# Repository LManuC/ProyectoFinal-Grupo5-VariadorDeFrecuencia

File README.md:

# ProyectoFinal-Grupo5-VariadorDeFrecuencia
El presente proyecto propone el desarrollo de un dispositivo electrónico capaz de alimentar un motor trifásico de hasta 1/3 HP, utilizando como fuente una tensión continua de 12V. Este conversor funciona como un variador de frecuencia, generando una salida trifásica con tensión eficaz entre fases de hasta 220 Vrms y frecuencia de salida variable entre 1 Hz y 150 Hz.
Para lograr el control del motor, se utiliza una técnica de modulación espacial (Space Vector Modulation), sin sensores montados en el eje del motor, lo que permite una instalación más sencilla, sin necesidad de encoder. El sistema está comandado por un controlador que gestiona tanto el disparo de los transistores como la interfaz de usuario y las protecciones internas.
El sistema estará contenido en una carcasa plástica especialmente diseñada para garantizar seguridad eléctrica durante la manipulación, proteger los componentes internos y permitir un montaje simple y robusto en el entorno de uso.

# Motivación
En un país como la Argentina, con grandes extensiones de tierras sin suministro eléctrico, la explotación de la energía renovable ha dado lugar a la utilización de grandes máquinas y herramientas eléctricas que tiempo atrás no hubiese sido posible. Si bien es cierto que los generadores eléctricos han dado espacio a estas instalaciones, requerían de mantenimiento periódico para que estuviesen operativas en el momento que se necesitaban, además de necesitar un material combustible que les permitiera funcionar y, en ocasiones podría generar un problema el ruido de los motores.

# Concepto del negocio
El dispositivo diseñado permitirá la conversión, acondicionamiento y regulación de la energía eléctrica para el accionamiento de un motor trifásico de baja potencia (1/3 HP) con velocidad variable generada a partir del motor de combustión interna y el alternador de equipos agrícolas o sistemas de energía solar, eólica con su correspondiente back up de energía eléctrica, posibilitando la operación de motores trifásicos destinados a tareas como sistemas de riego, transporte de materiales mediante cintas motorizadas o procesos de molienda integrados a bordo que puedan emplearse unificando todos los dispositivos que son empleados en instalaciones de energía renovable: Elevadores de tensión, inversores y variadores de frecuencia. La propuesta se enmarca en la necesidad de implementar soluciones energéticas autónomas y portátiles en entornos rurales, donde las condiciones de acceso a la red eléctrica convencional pueden ser limitadas o inexistentes.

## FODA

### Fortalezas
* La alimentación de baja tensión, nos permite meternos en un nuevo nicho. Permite trabajar con sistemas solares reducidos o baterías.
* Producto robusto y económico.
* Mantenimiento preventivo y reparación: Al conocer el diseño del equipo se puede hacer mantenimiento a los equipos y también otorgar una garantía con un taller de revisión y reparación en caso de falla.
* Productor local: Es una característica muy importante ya que el cliente tiene mayor confianza y los plazos de entrega son muchos más rápidos y económicos.
### Oportunidades
* Dada la practicidad puede ocasionar una gran demanda en zonas aisladas, remotas o rurales que se encuentren offgrid.
* Dado que es un único producto de su clase podría aparecer un nuevo rubro o sector diferente en donde encuentre utilidad. 
* El desarrollo nacional nos puede dar ventajas en licitaciones públicas o incentivos tecnológicos del gobierno.
### Debilidades
* Falta de experiencia y desconocimiento del producto puede desalentar o generar desconfianza en el producto.
* La robustez es muy importante en un controlador de un motor, se necesitan años de estudio riguroso del comportamiento y testeo del equipo para asegurar un funcionamiento ejemplar.
* La certificación eléctrica es un aspecto crucial en un equipo de esta clase y estas son muy costosas.
### Amenazas
* Posibilidad de la aparición de competencia con mejores precios y más funcionalidades.
* La escalabilidad no siempre es tan lineal, si aumenta mucho el mercado puede ocurrir que la inversión sea grande.
* El soporte post venta debe funcionar bien ya que en caso de una respuesta lenta al cliente podría perjudicar a la reputación de la marca.

# Alcance
El alcance del proyecto quedará definido en lograr, a partir de una fuente de de 12V de corriente contínua, el accionamiento de un motor trifásico de ⅓ de HP, variar su velocidad de giro, programar sesiones de trabajo diario, informar por señales típicas de 0-10V la velocidad de operación del motor, parada de emergencia, configuración de velocidades a través de un selector.

## Características eléctricas del dispositivo
Vin: 12VDC
Vout: 3 x 220VAC
fout: 0Hz - 150Hz
Pmax: 375W / 1/2HP

# Riesgos
1.  Fallas en la elección de la topología:
    -  Priorización del diseño frente a otras tareas;
    -  Ensayos varios sobre circuitos físicos;
2.  Rendimiento simulado insuficiente
    -  Priorización del diseño frente a otras tareas;
    -  Ensayos varios sobre circuitos físicos;
    -  Pruebas sobre motores utilizando variadores de frecuencia comerciales con entrada de contínua;
3.  No se consiguen los materiales en el mercado local
    -  Diseño temprano de PCB
    -  Compra en exceso de dispositivos críticos
4.  El transformador está mal construído y no entrega la potencia necesaria
    -  Fabricación de transformador con un proveedor especializado
5.  Al PCB le faltaron rutear una o más pistas
    -  Validaciones cruzadas de footprints
    -  Validaciones cruzadas de esquemáticos
    -  Validaciones cruzadas de PCB
6.  Pérdida de componentes
    -  Compra en exceso de dispositivos críticos
    -  Compra en exceso de dispositivos pequeños
    -  Compra en exceso de dispositivos sin marking
7.  Error en el diseño del footprint
    -  Validaciones cruzadas de footprints
    -  Checkbox en componentes para registrar validación
    -  Agregado de hoja de datos al esquemático
    -  Agregado de nombre del componente según el fabricante
8.  Errores de diseño hacen que la tensión no sea lo suficientemente alta
    -  Diseño autodefensivo con tensiones sobredimensionadas
    -  Cálculo de convertido con duty de respaldo
9. Rotura del banco de pruebas
    -  Fabricación de partes críticas de repuesto
    -  Colaboración externa especializada
10. Dificultades para simular el desfasaje
    -  Sobreestimación de los tiempos de trabajo
11. Error en el cálculo de la corriente máxima de algún componente y la corriente quedó sobredimensionada
    -  Justificación y documentación de los componentes elegidos
    -  Compra en exceso de dispositivos críticos
12. Falla el circuito y se quema una de las placas de potencia
    -  Fabricación de placa extra
    -  Compra en exceso de dispositivos críticos
    -  Circuitería de protección ruteada sin montar
13. El transformador está mal calculado y no entrega la potencia necesaria
    -  Ensayos exhaustivos durante el diseño
14. Ruido eléctrico interfiere en el display
    -  Fabricación de pantalla metálica para separar circuitos ruidosos
15. El motor no arranca por falta de potencia en la entrada
    -  Pruebas con batería de auto de respaldo

# Calidad

|Funcionalidad                     |  Importancia  |
|----------------------------------|---------------|
|Tensión de salida                 |  16,3%        |
|Tensión entrada                   |  20,7%        |
|Frecuencia de salida              |   7,1%        |
|Protecciones contra sobrecorriente|   6,9%        |
|Aislamiento entrada salida        |  12,1%        |
|Algoritmo modulación              |   9,6%        |
|Display con menú                  |  10,6%        |
|GPIOs                             |   7,7%        |
|Access point                      |   9,0%        |

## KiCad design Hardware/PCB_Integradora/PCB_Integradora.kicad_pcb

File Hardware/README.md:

# Comunicación entre microcontraldores

## 1. UART (Universal Asynchronous Receiver/Transmitter)
_Tipo:_ Asíncrona

_Velocidad típica:_ Hasta 1 Mbps (aunque la mayoría trabaja entre 9600 y 115200 bps)

_Ventajas:_
* Muy simple de implementar (incluso por software si no hay hardware UART)
* No necesita reloj compartido

_Desventajas:_
* Sin verificación de integridad robusta
* Solo útil para distancias cortas

_Ideal para:_ Comunicación punto a punto a distancias cortas y baja/moderada velocidad

## 2. SPI (Serial Peripheral Interface)
_Tipo:_ Síncrona (requiere línea de reloj)

_Velocidad típica:_ De 1 a 20 Mbps (puede llegar a más dependiendo del microcontrolador)

_Ventajas:_
* Muy rápida
* Full duplex
* Buena para cortas distancias dentro de un mismo PCB

_Desventajas:_
* Requiere más pines (MOSI, MISO, SCLK y a veces CS)
* No hay detección de errores integrada

_Ideal para:_ Comunicación rápida entre micros en un mismo sistema o módulo

## Conclusión

Elegimos SPI por subre UART para poder aprovechar más la velocidad del bus. Creemos que la implemetación en software no debería cambiar entre una u otra, por lo que no habría una ventaja o desventaja de una sobre la otra.

Debemos tener el cuidado suficiente de la con la señal ya que, pese a ser un único producto y un ansamblado fijo, la comunicación se dará entre dos PCBs diferentes a través de un header.

# Pulsadores

Para el traclado matricial utilizaremos los pulsadores con vástago sobresaliente para poder enganchar con la tecla impresa.

# Teclado

Utilizar por lo menos 8 teclas, pero no más (o no mucho más de 10).

El Start y stop cuentan dentro de este teclaod matricial pero el botón golpe de puño para parada de emergencia iría aparte.

Usaríamos un relay para cortar en bus de contínua, comandado por la parada de emergencia y el STM32.

# Dimensiones

El gabinete va a tener un tamaño de 130mm x 325mm (Sujeto a modificaciones) para respetar una relación de aspecto de 2.5.

La idea sería incluir en la parte superior un cooler de 120mm de lado.

# Señales a medir por el ESP

* Nivel de tensión del bus de contínua
* Corriente del bus de contínua

# Conectores

## Señales para el ADC
1. 5V
2. GND
3. Corriente
4. Tensión
5. GND

## Comunicaciones
1. GND
2. NSS
3. SCK
4. MISO
5. MOSI

## Señales de una placa a la otra

1. 0-10V
2. Selección de velocidades
3. Start
4. Stop

## Botones de start y stop

Borneras externas para conectar pulsadores externos en caso de montar el gabinete del producto dentro de otro gabinete.

# Alimentación

1. +12V
2. GND

1. +5V
2. GND

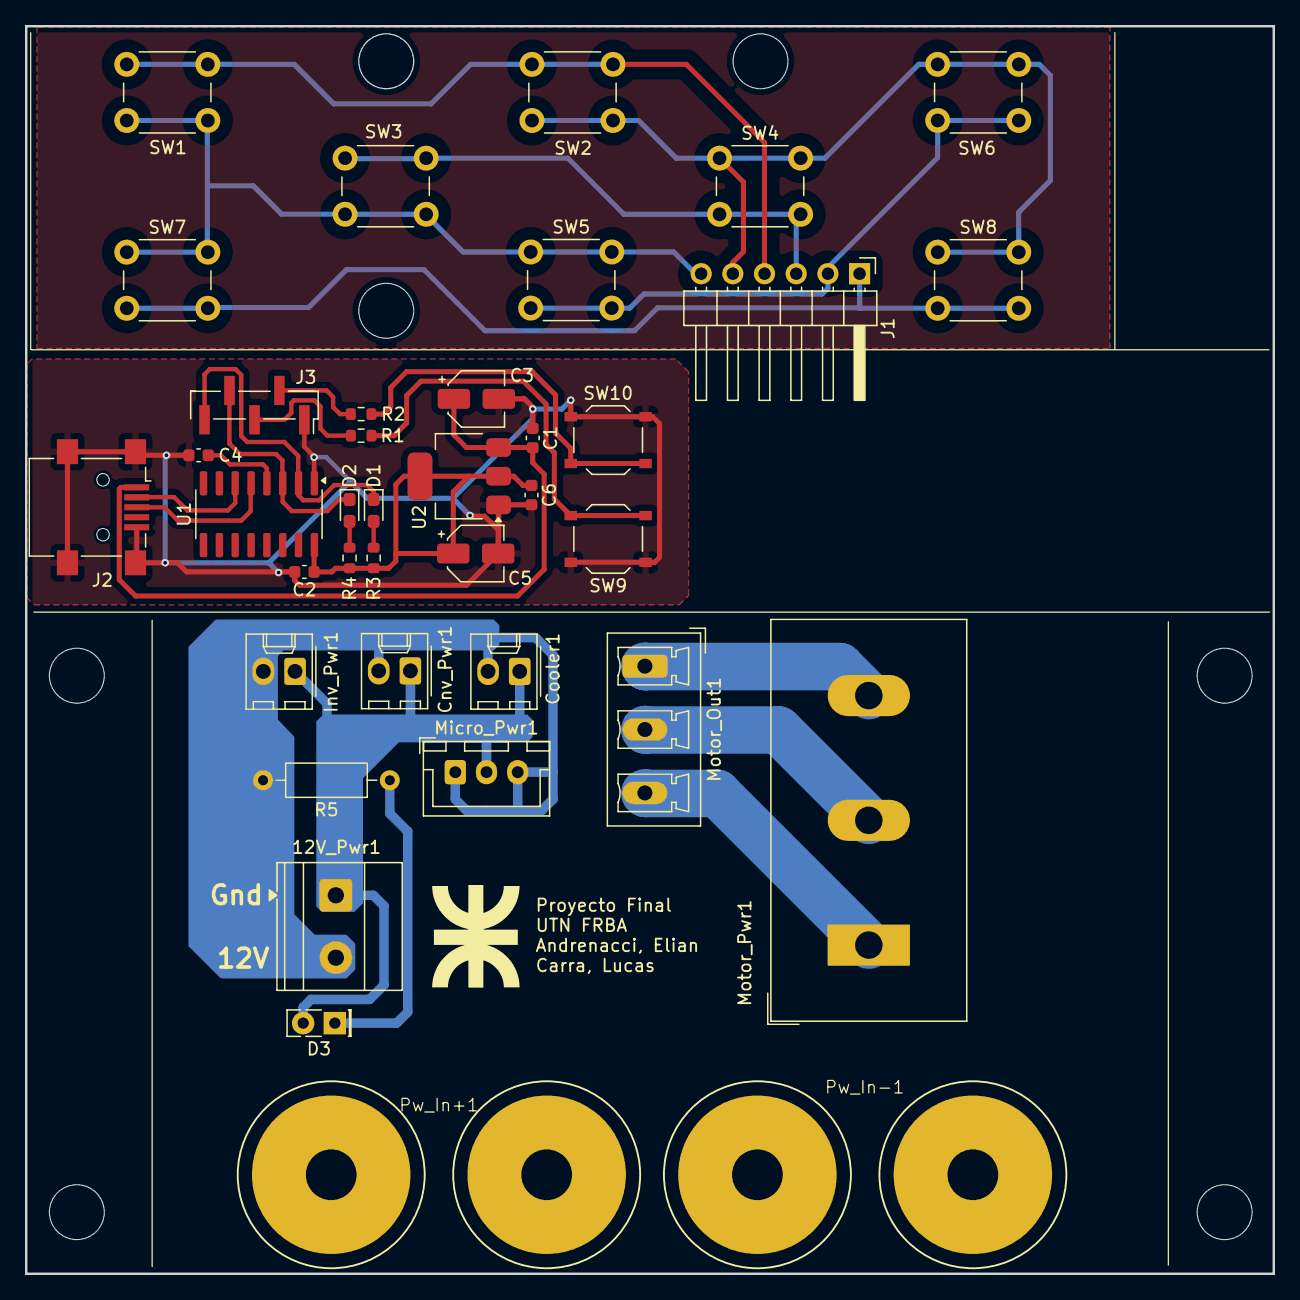
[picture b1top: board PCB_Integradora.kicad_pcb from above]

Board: 2 copper layers, 100.0 x 100.0 mm, 38 parts (0 on the bottom side), 26 nets.

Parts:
12V_Pwr1: Screw_Terminal_01x02; TerminalBlock_Phoenix_MKDS-1,5-2_1x02_P5.00mm_Horizontal
C1, C6: 1uF; C_0603_1608Metric
C2, C4: 1nF; C_0603_1608Metric
C3: 10uF; CP_Elec_4x5.4
C5: 22uF; CP_Elec_4x5.4
Cnv_Pwr1: Conn_01x02; Molex_KK-254_AE-6410-02A_1x02_P2.54mm_Vertical
Cooler1: Conn_01x02; Molex_KK-254_AE-6410-02A_1x02_P2.54mm_Vertical
D1, D2: LED; LED_0603_1608Metric_Pad1.05x0.95mm_HandSolder
D3: LED_Green; LED_Rectangular_W5.0mm_H2.0mm
Inv_Pwr1: Conn_01x02; Molex_KK-254_AE-6410-02A_1x02_P2.54mm_Vertical
J1: Conn_01x06; PinHeader_1x06_P2.54mm_Horizontal
J2: USB_OTG; USB_Mini-B_Lumberg_2486_01_Horizontal
J3: Conn_01x05_Pin; PinHeader_1x05_P2.00mm_Vertical_SMD_Pin1Right
Micro_Pwr1: Conn_01x03; JST_XH_B3B-XH-A_1x03_P2.50mm_Vertical
Motor_Out1: Conn_01x03; PhoenixContact_MCV_1,5_3-G-5.08_1x03_P5.08mm_Vertical
Motor_Pwr1: Screw_Terminal_01x03; TerminalBlock_Dinkle_DT-55-B01X-03_P10.00mm
Pw_In+1: Conn_01x02; BananaSocket - 2P - 4mm
Pw_In-1: Conn_01x02; BananaSocket - 2P - 4mm
R1, R2, R3, R4: 221; R_0603_1608Metric
R5: 1.2k; R_Axial_DIN0207_L6.3mm_D2.5mm_P10.16mm_Horizontal
SW1, SW2, SW3, SW4, SW5, SW6, SW7, SW8: SW_Push; SW_PUSH_6mm
SW9, SW10: SW_MEC_5E; SW_Push_1P1T_XKB_TS-1187A
U1: CH340C; SOIC-16_3.9x9.9mm_P1.27mm
U2: AMS1117-3.3; SOT-223-3_TabPin2

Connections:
+3.3V: C2.1, C5.1, C6.1, R3.1, R4.1, U1.16 (VCC), U2.2 (VO)
+5V: C1.1, C3.1, J2.1 (VBUS), U2.3 (VI)
/ESP Programadora/BOOT_prog: J3.2, R2.1
/ESP Programadora/ENABLE: J3.3, R1.1
/ESP Programadora/Rx: D2.1 (K), J3.4, U1.3 (RXD)
/ESP Programadora/Tx: D1.1 (K), J3.5, U1.2 (TXD)
/Interfaz HMI/Matrix_0: J1.1, SW7.2, SW8.2
/Interfaz HMI/Matrix_1: J1.2, SW5.2, SW6.2
/Interfaz HMI/Matrix_2: J1.3, SW3.2, SW4.2
/Interfaz HMI/Matrix_3: J1.4, SW1.2, SW2.2
/Interfaz HMI/Matrix_4: J1.5, SW2.1, SW4.1, SW6.1, SW8.1
/Interfaz HMI/Matrix_5: J1.6, SW1.1, SW3.1, SW5.1, SW7.1
/Interfaz de conexión/12V_Cnv: 12V_Pwr1.1, Cnv_Pwr1.1, Cooler1.1, D3.2 (A), Inv_Pwr1.1, Micro_Pwr1.2
/Interfaz de conexión/Gnd_Cnv: 12V_Pwr1.2, Cnv_Pwr1.2, Cooler1.2, Inv_Pwr1.2, Micro_Pwr1.1, Micro_Pwr1.3, R5.2
GND: C1.2, C2.2, C3.2, C4.1, C5.2, C6.2, J2.5 (GND), J2.6 (Shield), J3.1, SW9.1, SW9.2, SW10.1, SW10.2, U1.1 (GND), U2.1 (GND)
unnamed: D1.2 (A), R3.2
unnamed: D2.2 (A), R4.2
unnamed: D3.1 (K), R5.1
unnamed: J2.3 (D+), U1.5 (UD+)
unnamed: J2.2 (D-), U1.6 (UD-)
unnamed: Motor_Out1.1, Motor_Pwr1.3
unnamed: Motor_Out1.2, Motor_Pwr1.2
unnamed: Motor_Out1.3, Motor_Pwr1.1
unnamed: R1.2, SW9.3 (K), SW9.4 (A)
unnamed: R2.2, SW10.3 (K), SW10.4 (A)
unnamed: C4.2, U1.4 (V3)

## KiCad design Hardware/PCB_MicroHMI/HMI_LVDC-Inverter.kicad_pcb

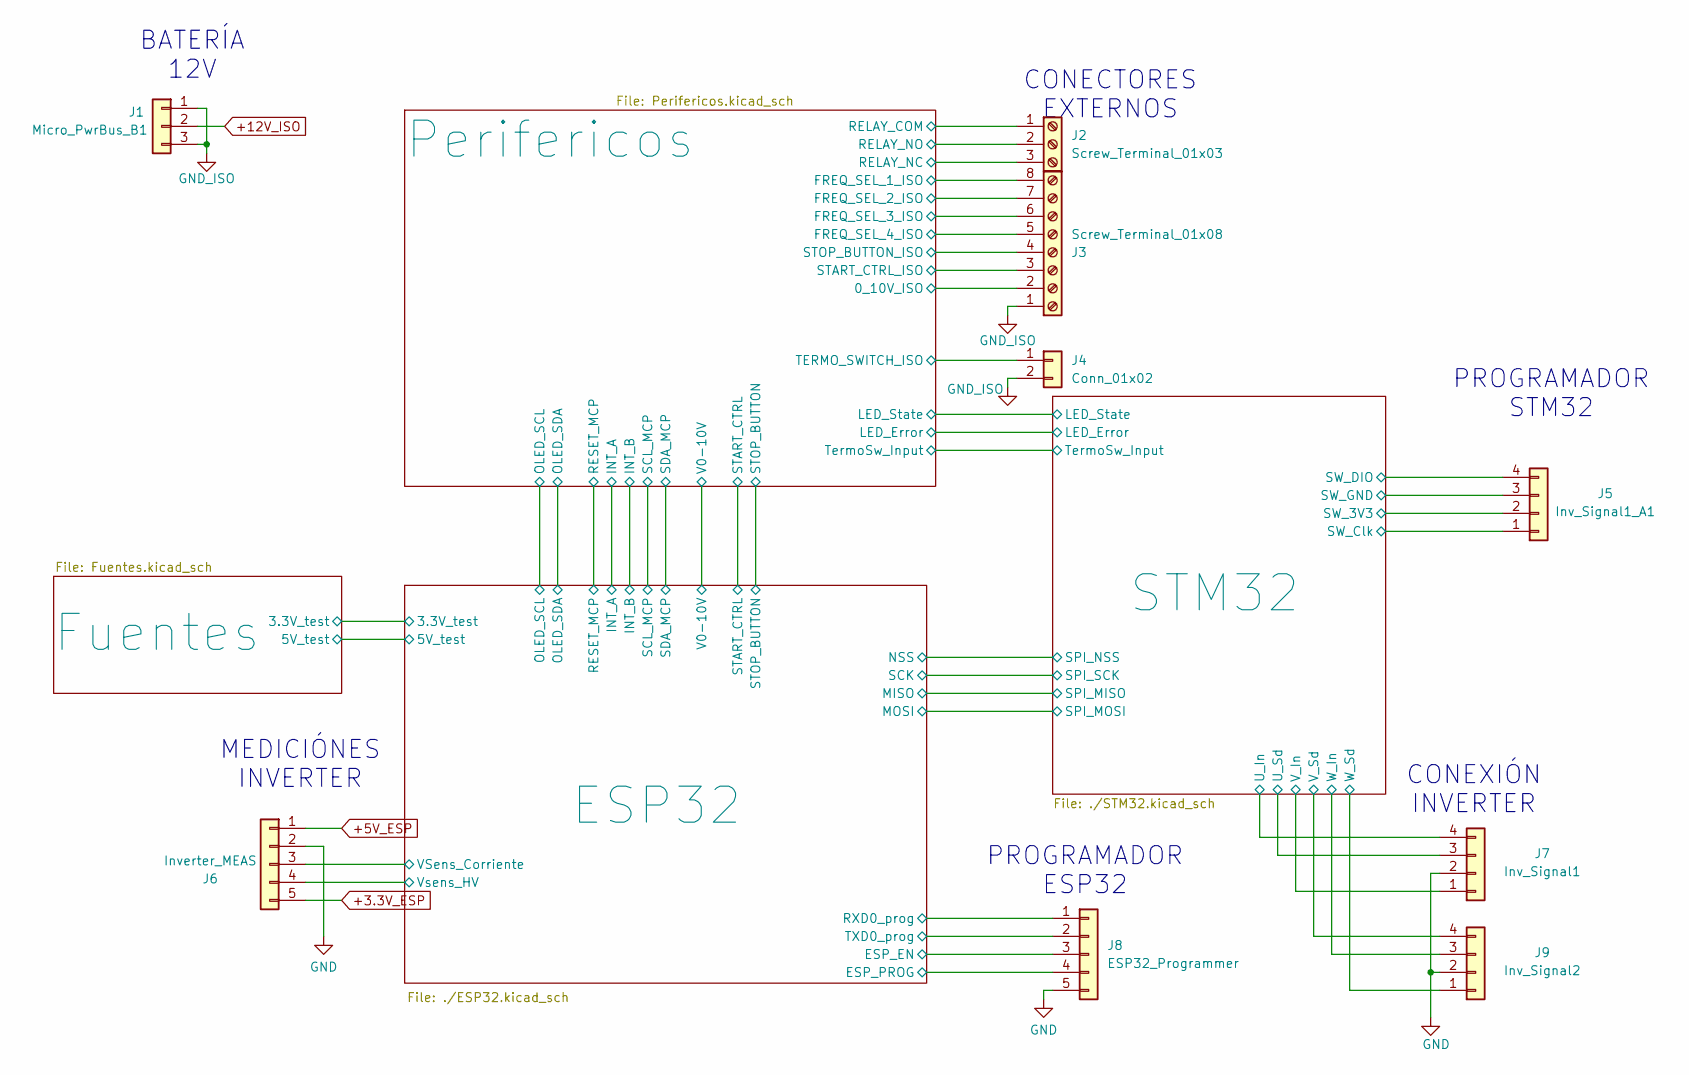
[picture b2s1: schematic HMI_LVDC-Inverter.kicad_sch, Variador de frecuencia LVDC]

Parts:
J1: Micro_PwrBus_B1; JST_XH_B3B-XH-A_1x03_P2.50mm_Vertical
J2: Screw_Terminal_01x03; TerminalBlock_Degson_DG250-3.5-03P_1x03_P3.50mm_45Degree
J3: Screw_Terminal_01x08; TerminalBlock_Degson_DG250-3.5-08P_1x08_P3.50mm_45Degree
J4: Conn_01x02; JST_XH_B2B-XH-A_1x02_P2.50mm_Vertical
J5: Inv_Signal1_A1; PinHeader_1x04_P2.54mm_Vertical
J6: Inverter_MEAS; JST_XH_B5B-XH-A_1x05_P2.50mm_Vertical
J7: Inv_Signal1; JST_XH_B4B-XH-A_1x04_P2.50mm_Vertical
J8: ESP32_Programmer; PinHeader_1x05_P2.54mm_Vertical
J9: Inv_Signal2; JST_XH_B4B-XH-A_1x04_P2.50mm_Vertical

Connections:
+3.3V_ESP: J6.5; also elsewhere on the board
+5V_ESP: J6.1; also elsewhere on the board
+12V_ISO: J1.2; also elsewhere on the board
/ESP32/BOOT_prog: J8.4; also elsewhere on the board
/ESP32/ENABLE: J8.3; also elsewhere on the board
/ESP32/RXD0_prog: J8.1; also elsewhere on the board
/ESP32/TXD0_prog: J8.2; also elsewhere on the board
/ESP32/VSens_Corriente: J6.3; also elsewhere on the board
/ESP32/Vsens_HV: J6.4; also elsewhere on the board
/Perifericos/0_10V_ISO: J3.2; also elsewhere on the board
/Perifericos/FREQ_SEL_1_ISO: J3.8; also elsewhere on the board
/Perifericos/FREQ_SEL_2_ISO: J3.7; also elsewhere on the board
/Perifericos/FREQ_SEL_3_ISO: J3.6; also elsewhere on the board
/Perifericos/FREQ_SEL_4_ISO: J3.5; also elsewhere on the board
/Perifericos/RELAY_COM: J2.1; also elsewhere on the board
/Perifericos/RELAY_NC: J2.3; also elsewhere on the board
/Perifericos/RELAY_NO: J2.2; also elsewhere on the board
/Perifericos/START_CTRL_ISO: J3.3; also elsewhere on the board
/Perifericos/STOP_BUTTON_ISO: J3.4; also elsewhere on the board
/Perifericos/TERMO_SWITCH_ISO: J4.1; also elsewhere on the board
/STM32/SW_3V3: J5.2; also elsewhere on the board
/STM32/SW_Clk: J5.1; also elsewhere on the board
/STM32/SW_DIO: J5.4; also elsewhere on the board
/STM32/U_In: J7.4; also elsewhere on the board
/STM32/U_Sd: J7.3; also elsewhere on the board
/STM32/V_In: J7.1; also elsewhere on the board
/STM32/V_Sd: J9.4; also elsewhere on the board
/STM32/W_In: J9.3; also elsewhere on the board
/STM32/W_Sd: J9.1; also elsewhere on the board
GND: J5.3, J6.2, J7.2, J8.5, J9.2; also elsewhere on the board
GND_ISO: J1.1, J1.3, J3.1, J4.2; also elsewhere on the board

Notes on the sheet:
CONEXIÓN INVERTER
PROGRAMADOR ESP32
PROGRAMADOR STM32
BATERÍA 12V
MEDICIÓNES INVERTER
CONECTORES EXTERNOS

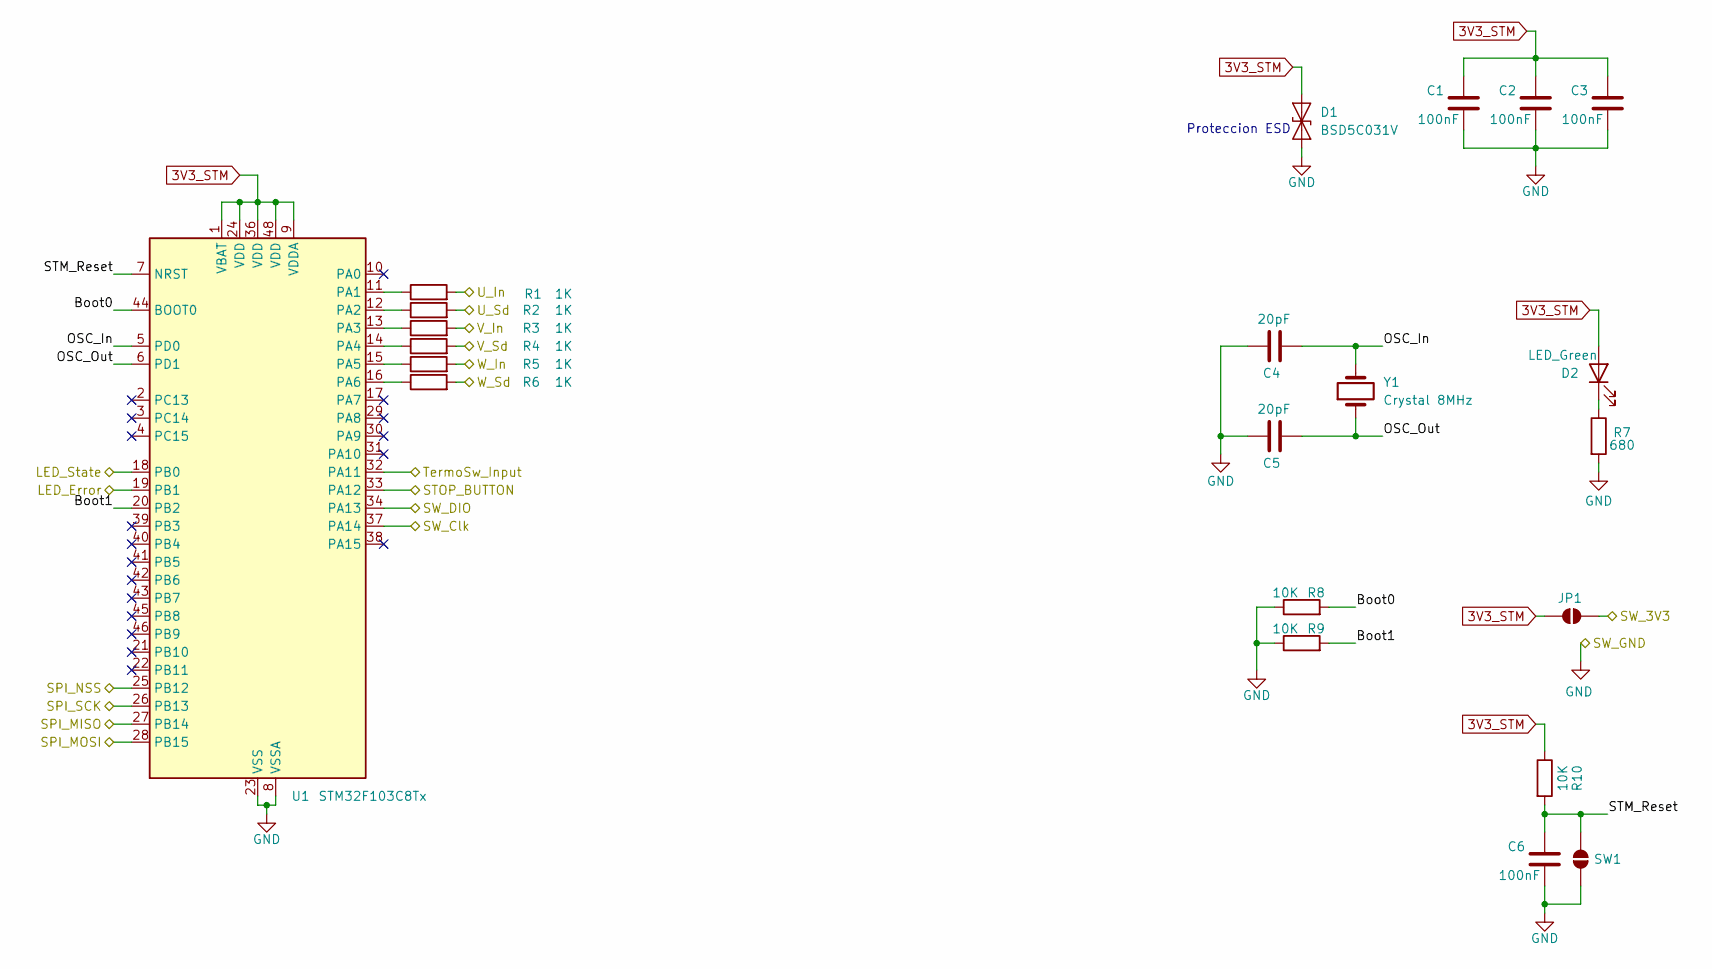
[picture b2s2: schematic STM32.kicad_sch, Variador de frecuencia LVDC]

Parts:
C1, C2, C3, C6: 100nF; C_0603_1608Metric_Pad1.08x0.95mm_HandSolder
C4, C5: 20pF; C_0603_1608Metric_Pad1.08x0.95mm_HandSolder
D1: BSD5C031V; D_SOD-523
D2: LED_Green; LED_0603_1608Metric_Pad1.05x0.95mm_HandSolder
JP1: SolderJumper_2_Open; SolderJumper-2_P1.3mm_Open_RoundedPad1.0x1.5mm
R1, R2, R3, R4, R5, R6: 1K; R_0603_1608Metric_Pad0.98x0.95mm_HandSolder
R7: 680; R_0603_1608Metric_Pad0.98x0.95mm_HandSolder
R8, R9, R10: 10K; R_0603_1608Metric_Pad0.98x0.95mm_HandSolder
SW1: SolderJumper_2_Open; SolderJumper-2_P1.3mm_Open_RoundedPad1.0x1.5mm
U1: STM32F103C8Tx; LQFP-48_7x7mm_P0.5mm
Y1: Crystal 8MHz; Crystal_SMD_5032-2Pin_5.0x3.2mm

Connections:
3V3_STM: C1.1, C2.1, C3.1, D1.2 (A2), D2.2 (A), JP1.1 (A), R10.1, U1.1 (VBAT), U1.9 (VDDA), U1.24 (VDD), U1.36 (VDD), U1.48 (VDD); also elsewhere on the board
/ESP32/MISO: U1.27 (PB14); also elsewhere on the board
/ESP32/MOSI: U1.28 (PB15); also elsewhere on the board
/ESP32/NSS: U1.25 (PB12); also elsewhere on the board
/ESP32/SCK: U1.26 (PB13); also elsewhere on the board
/Perifericos/LED_Error: U1.19 (PB1); also elsewhere on the board
/Perifericos/LED_State: U1.18 (PB0); also elsewhere on the board
/Perifericos/TermoSw_Input: U1.32 (PA11); also elsewhere on the board
/STM32/Boot0: R8.2, U1.44 (BOOT0)
/STM32/Boot1: R9.2, U1.20 (PB2)
/STM32/OSC_In: C4.1, U1.5 (PD0), Y1.2
/STM32/OSC_Out: C5.1, U1.6 (PD1), Y1.1
/STM32/STM_Reset: C6.1, R10.2, SW1.2 (B), U1.7 (NRST)
/STM32/STOP_BUTTON: U1.33 (PA12)
/STM32/SW_3V3: JP1.2 (B); also elsewhere on the board
/STM32/SW_Clk: U1.37 (PA14); also elsewhere on the board
/STM32/SW_DIO: U1.34 (PA13); also elsewhere on the board
/STM32/U_In: R1.2; also elsewhere on the board
/STM32/U_Sd: R2.2; also elsewhere on the board
/STM32/V_In: R3.2; also elsewhere on the board
/STM32/V_Sd: R4.2; also elsewhere on the board
/STM32/W_In: R5.2; also elsewhere on the board
/STM32/W_Sd: R6.2; also elsewhere on the board
GND: C1.2, C2.2, C3.2, C4.2, C5.2, C6.2, D1.1 (A1), R7.2, R8.1, R9.1, SW1.1 (A), U1.8 (VSSA), U1.23 (VSS), U1.35 (VSS), U1.47 (VSS); also elsewhere on the board
unnamed: D2.1 (K), R7.1
unnamed: R1.1, U1.11 (PA1)
unnamed: R2.1, U1.12 (PA2)
unnamed: R3.1, U1.13 (PA3)
unnamed: R4.1, U1.14 (PA4)
unnamed: R5.1, U1.15 (PA5)
unnamed: R6.1, U1.16 (PA6)

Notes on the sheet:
Proteccion ESD

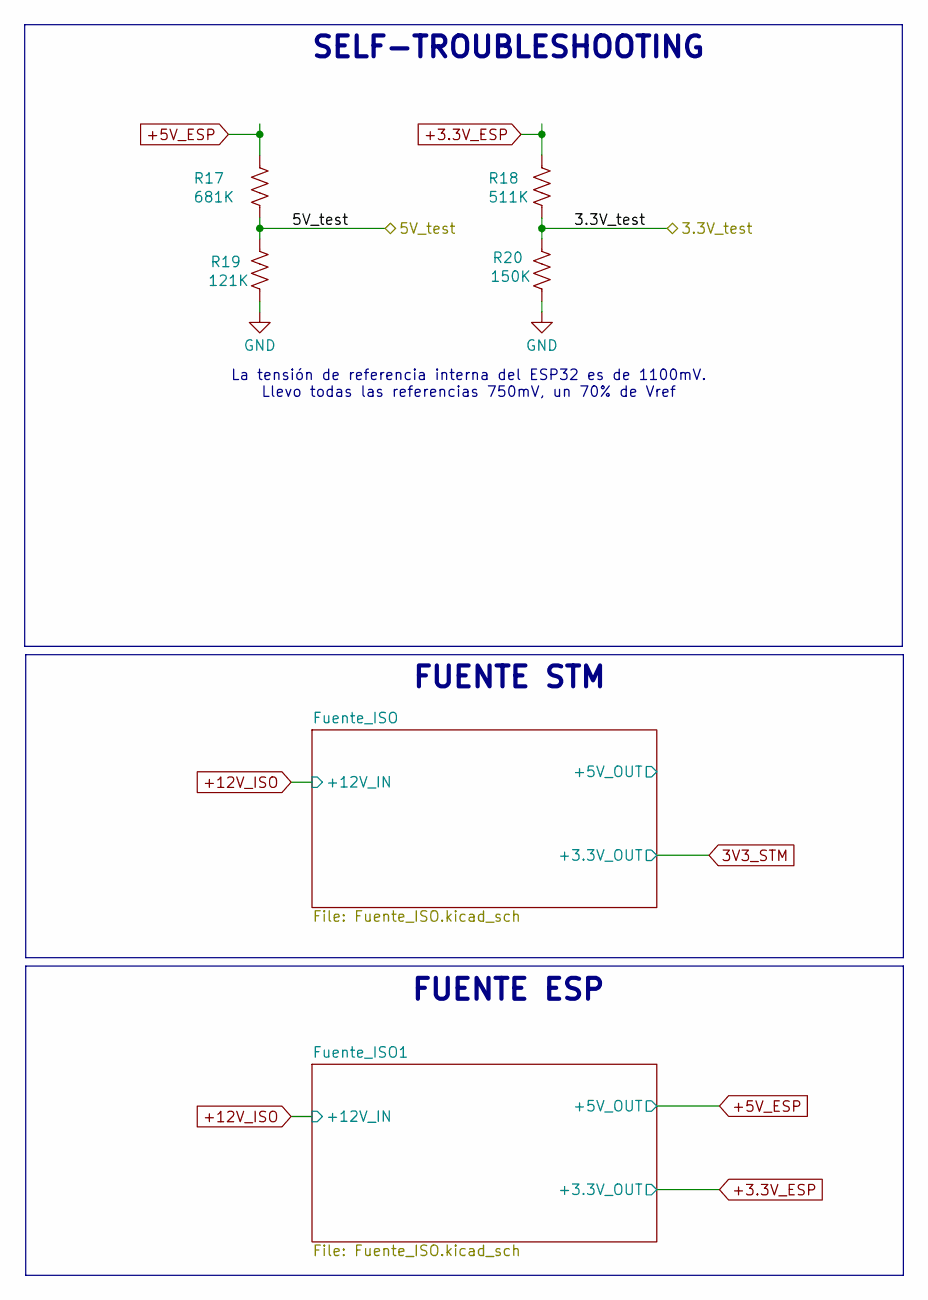
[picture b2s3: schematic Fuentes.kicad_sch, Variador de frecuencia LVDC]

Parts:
R17: 681K; R_0603_1608Metric_Pad0.98x0.95mm_HandSolder
R18: 511K; R_0603_1608Metric_Pad0.98x0.95mm_HandSolder
R19: 121K; R_0603_1608Metric_Pad0.98x0.95mm_HandSolder
R20: 150K; R_0603_1608Metric_Pad0.98x0.95mm_HandSolder

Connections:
+3.3V_ESP: R18.1; also elsewhere on the board
+5V_ESP: R17.1; also elsewhere on the board
/ESP32/3.3V_test: R18.2, R20.1; also elsewhere on the board
/ESP32/5V_test: R17.2, R19.1; also elsewhere on the board
GND: R19.2, R20.2; also elsewhere on the board

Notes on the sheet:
FUENTE ESP
FUENTE STM
SELF-TROUBLESHOOTING
La tensión de referencia interna del ESP32 es de 1100mV. Llevo todas las referencias 750mV, un 70% de Vref

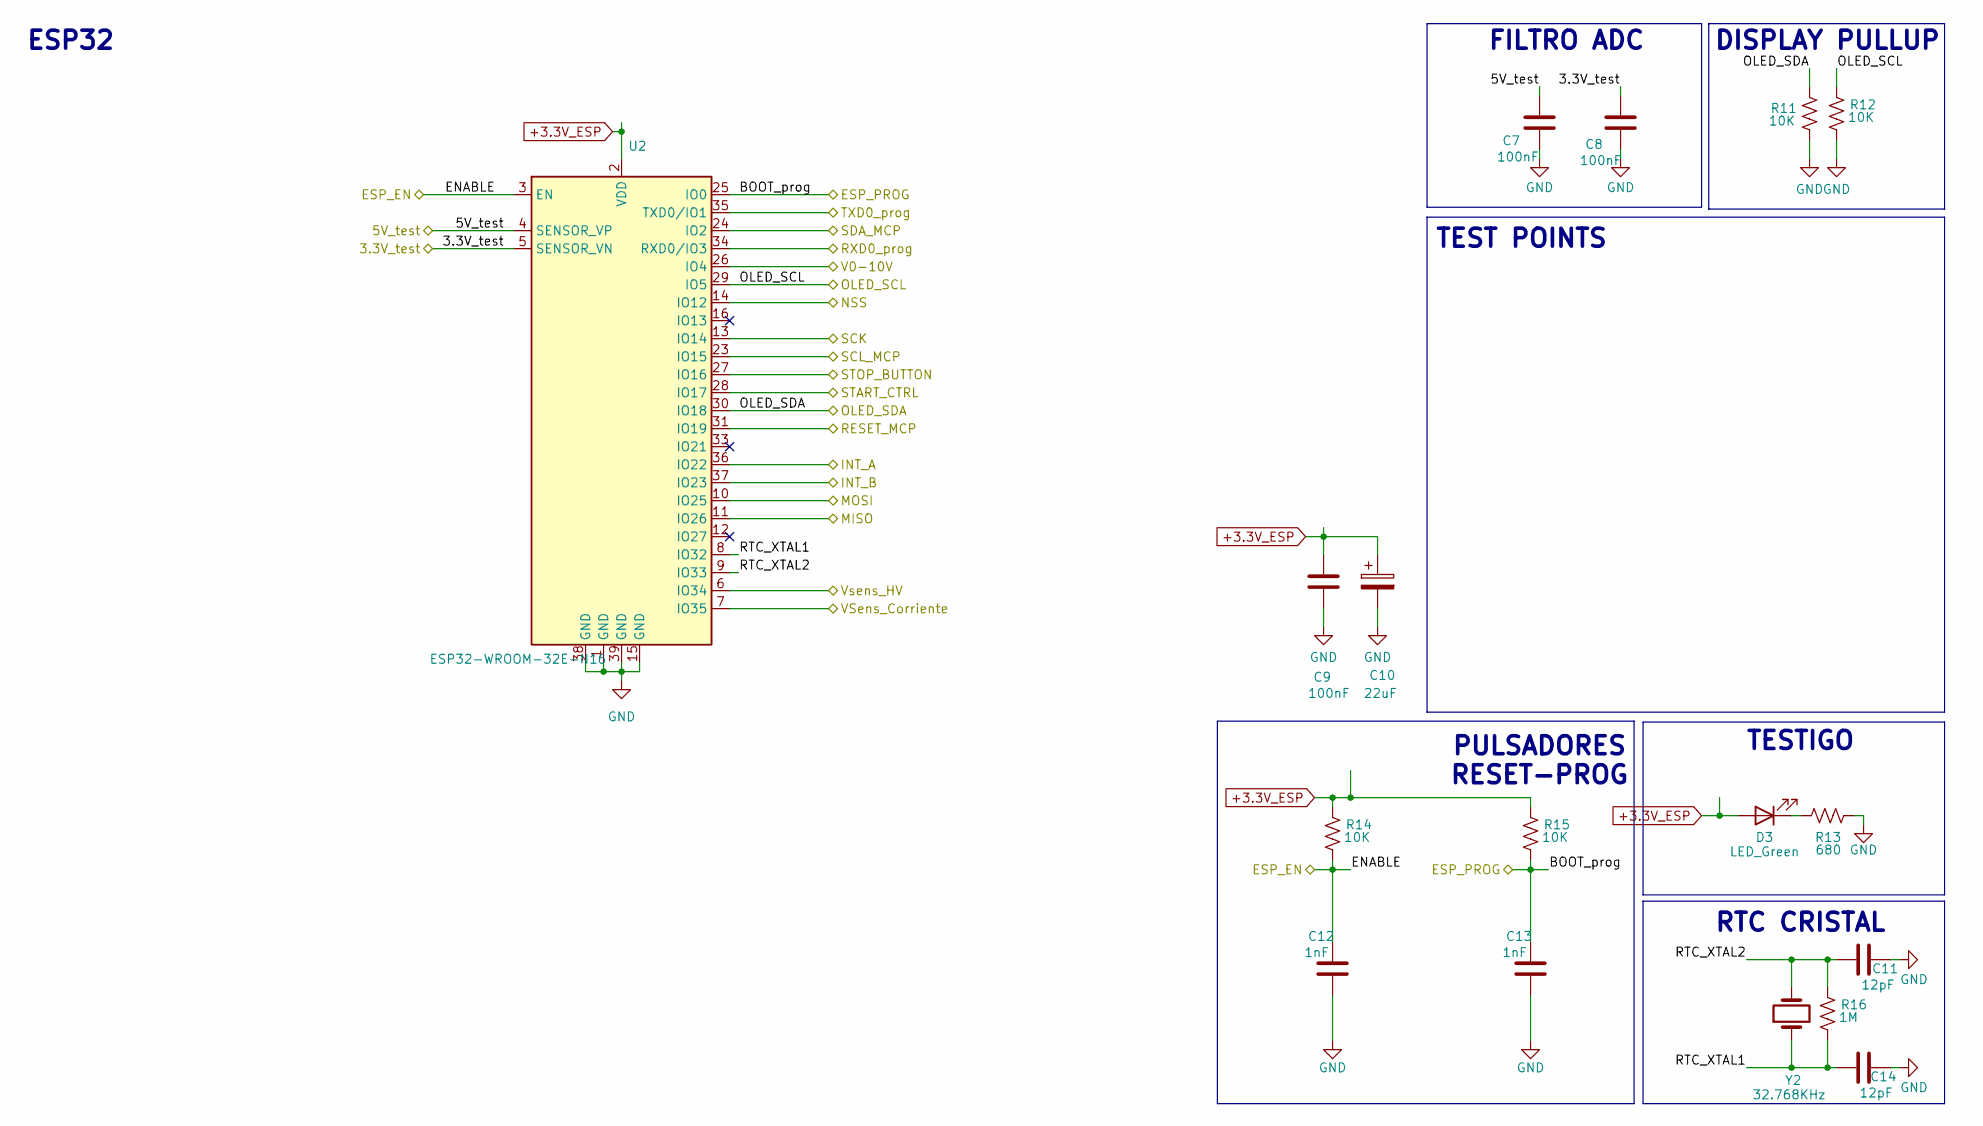
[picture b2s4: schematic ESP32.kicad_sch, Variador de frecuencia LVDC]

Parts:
C7, C8, C9: 100nF; C_0603_1608Metric_Pad1.08x0.95mm_HandSolder
C10: 22uF; CP_Elec_5x5.4
C11, C14: 12pF; C_0603_1608Metric
C12, C13: 1nF; C_0603_1608Metric
D3: LED_Green; LED_0603_1608Metric_Pad1.05x0.95mm_HandSolder
R11, R12, R14, R15: 10K; R_0603_1608Metric_Pad0.98x0.95mm_HandSolder
R13: 680; R_0603_1608Metric_Pad0.98x0.95mm_HandSolder
R16: 1M; R_0603_1608Metric_Pad0.98x0.95mm_HandSolder
U2: ESP32-WROOM-32E-N16; ESP32-WROOM-32E
Y2: 32.768KHz; Crystal_SMD_3215-2Pin_3.2x1.5mm

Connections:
+3.3V_ESP: C9.1, C10.1, D3.2 (A), R14.1, R15.1, U2.2 (VDD); also elsewhere on the board
/ESP32/3.3V_test: C8.1, U2.5 (SENSOR_VN); also elsewhere on the board
/ESP32/5V_test: C7.1, U2.4 (SENSOR_VP); also elsewhere on the board
/ESP32/BOOT_prog: C13.1, R15.2, U2.25 (IO0); also elsewhere on the board
/ESP32/ENABLE: C12.1, R14.2, U2.3 (EN); also elsewhere on the board
/ESP32/INT_A: U2.36 (IO22); also elsewhere on the board
/ESP32/INT_B: U2.37 (IO23); also elsewhere on the board
/ESP32/MISO: U2.11 (IO26); also elsewhere on the board
/ESP32/MOSI: U2.10 (IO25); also elsewhere on the board
/ESP32/NSS: U2.14 (IO12); also elsewhere on the board
/ESP32/OLED_SCL: R12.1, U2.29 (IO5); also elsewhere on the board
/ESP32/OLED_SDA: R11.1, U2.30 (IO18); also elsewhere on the board
/ESP32/RESET_MCP: U2.31 (IO19); also elsewhere on the board
/ESP32/RTC_XTAL1: C14.2, R16.2, U2.8 (IO32), Y2.1
/ESP32/RTC_XTAL2: C11.1, R16.1, U2.9 (IO33), Y2.2
/ESP32/RXD0_prog: U2.34 (RXD0/IO3); also elsewhere on the board
/ESP32/SCK: U2.13 (IO14); also elsewhere on the board
/ESP32/SCL_MCP: U2.23 (IO15); also elsewhere on the board
/ESP32/SDA_MCP: U2.24 (IO2); also elsewhere on the board
/ESP32/START_CTRL: U2.28 (IO17); also elsewhere on the board
/ESP32/STOP_BUTTON: U2.27 (IO16); also elsewhere on the board
/ESP32/TXD0_prog: U2.35 (TXD0/IO1); also elsewhere on the board
/ESP32/V0-10V: U2.26 (IO4); also elsewhere on the board
/ESP32/VSens_Corriente: U2.7 (IO35); also elsewhere on the board
/ESP32/Vsens_HV: U2.6 (IO34); also elsewhere on the board
GND: C7.2, C8.2, C9.2, C10.2, C11.2, C12.2, C13.2, C14.1, R11.2, R12.2, R13.2, U2.1 (GND), U2.15 (GND), U2.38 (GND), U2.39 (GND); also elsewhere on the board
unnamed: D3.1 (K), R13.1

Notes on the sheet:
DISPLAY PULLUP
ESP32
FILTRO ADC
TESTIGO
PULSADORES RESET-PROG
TEST POINTS
RTC CRISTAL

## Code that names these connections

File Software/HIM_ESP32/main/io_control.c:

#include "sdkconfig.h"

#include "esp_err.h"
#include "esp_log.h"

#include "driver/gpio.h"

#include "freertos/FreeRTOS.h"
#include "freertos/semphr.h"
#include "freertos/task.h"
#include "freertos/queue.h"

#include <inttypes.h>
#include <stdio.h>
#include <stdlib.h>

#include "esp32.h"
#include "STM32_comm.h"

#include "./MCP23017/MCP23017.h"

static const char *TAG = "IO_CTRL";

#define INT_A_PIN           GPIO_INPUT_IO_15

#define BUZZER_PIN          0
#define RELAY_CTRL_PIN      1
#define FREQ_SEL_1_PIN      2
#define FREQ_SEL_2_PIN      3
#define FREQ_SEL_3_PIN      4
#define FREQ_SEL_4_PIN      5
#define TERMO_SW_PIN        6

#define FREQ_SEL_MASK       (1 << FREQ_SEL_4_PIN) || (1 << FREQ_SEL_3_PIN) || (1 << FREQ_SEL_2_PIN) || (1 << FREQ_SEL_1_PIN)
#define TERMO_SW_MASK       (1 << TERMO_SW_PIN)

#define INT_B_PIN           GPIO_INPUT_IO_2

#define MATRIX_0_PIN        0
#define MATRIX_1_PIN        1
#define MATRIX_2_PIN        2
#define MATRIX_3_PIN        3
#define MATRIX_4_PIN        4
#define MATRIX_5_PIN        5

QueueHandle_t MCP23017_evt_queue = NULL;
uint8_t mcp_porta;
uint8_t mcp_portb;

void IRAM_ATTR gpio_isr_handler(void* arg) {
    uint32_t gpio_num = (uint32_t) arg;
    xQueueSendFromISR(MCP23017_evt_queue, &gpio_num, NULL);
}

void gpio_init_interrupts(void) {
    // Selecciono máscara de pines
    gpio_config_t io_conf = {
        .intr_type = GPIO_INTR_POSEDGE,    // interrupción en flanco ascendente
        .mode = GPIO_MODE_INPUT,
        .pin_bit_mask = (1ULL<<GPIO_INPUT_IO_2) | (1ULL<<GPIO_INPUT_IO_15),
        .pull_down_en = 0,
        .pull_up_en = 1
    };

    gpio_config(&io_conf);

    // Instalo servicio de ISR
    gpio_install_isr_service(ESP_INTR_FLAG_DEFAULT);

    // Asocio pines a la rutina ISR
    gpio_isr_handler_add(GPIO_INPUT_IO_2, gpio_isr_handler, (void*) GPIO_INPUT_IO_2);
    gpio_isr_handler_add(GPIO_INPUT_IO_15, gpio_isr_handler, (void*) GPIO_INPUT_IO_15);

    ESP_LOGI(TAG, "Interrupciones GPIO configuradas en IO2 y IO15");
}

void MCP23017_interrupt_attendance(void* arg) {
    
    MCP23017_INIT();
    gpio_init_interrupts();
    
    uint32_t io_num;
    uint8_t scratch_data;
    
    for(;;) {
        if(xQueueReceive(MCP23017_evt_queue, &io_num, portMAX_DELAY)) {
            ESP_LOGI(TAG, "Interrupción en GPIO[%ld], estado: %d", io_num, gpio_get_level(io_num));

            if ( io_num == INT_A_PIN ) {
                mcp_interrupt_flag(PORTA, &scratch_data);
                if ( scratch_data & TERMO_SW_MASK ) {
                    mcp_get_on_interrupt_input(PORTA, &mcp_porta);
                    comando_t cmd = CMD_PARADA_ROTAURA; 
                    xQueueSend(cmd_queue, &cmd, portMAX_DELAY);
                    /*
                     * Encola reporte de parada de emergencia al STM32
                    */
                } else if ( scratch_data & FREQ_SEL_MASK ) {
                    mcp_get_on_interrupt_input(PORTA, &mcp_porta);
                    scratch_data &= FREQ_SEL_MASK;                                                          // 00ss ss00
                    mcp_porta;
                    scratch_data = ( scratch_data >> FREQ_SEL_1_PIN );                                      // 0000 ssss
                    comando_t cmd = CMD_CAMBIO_VELOCIDAD; 
                    xQueueSend(cmd_queue, &cmd, portMAX_DELAY);
                    /*
                     * Encola reporte de cambio de velocidad al STM32
                    */
                }
            } else if ( io_num == INT_B_PIN ) {
                mcp_interrupt_flag(PORTB, &scratch_data);

            }
        }
    }
}

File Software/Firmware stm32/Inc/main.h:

/**
  * @file    main.h
  * @brief   Header de la aplicación principal.
  * @details Contiene definiciones comunes, asignación de pines y prototipos
  *          globales compartidos por todo el proyecto.
  */

#ifndef __MAIN_H
#define __MAIN_H

#include "stm32f1xx_hal.h"

/** \defgroup GPIO_SVM Pines del inversor (puerto A)
  * @brief Pines de control del módulo SVM en GPIOA.
  * @{
  */

/** @brief Entrada lógica de la pierna U (GPIOA, PIN_1). */
#define GPIO_U_IN           GPIO_PIN_1
/** @brief Shutdown/Habilitación driver pierna U (GPIOA, PIN_2). */
#define GPIO_U_SD           GPIO_PIN_2
/** @brief Entrada lógica de la pierna V (GPIOA, PIN_3). */
#define GPIO_V_IN           GPIO_PIN_3
/** @brief Shutdown/Habilitación driver pierna V (GPIOA, PIN_4). */
#define GPIO_V_SD           GPIO_PIN_4
/** @brief Entrada lógica de la pierna W (GPIOA, PIN_5). */
#define GPIO_W_IN           GPIO_PIN_5
/** @brief Shutdown/Habilitación driver pierna W (GPIOA, PIN_6). */
#define GPIO_W_SD           GPIO_PIN_6

/** @brief Entrada digital: Termo–switch (GPIOA, PIN_11). */
#define GPIO_TERMO_SWITCH   GPIO_PIN_11
/** @brief Entrada digital: Botón de parada (GPIOA, PIN_12). */
#define GPIO_STOP_BUTTON    GPIO_PIN_12
/** @} */

/** \defgroup GPIO_LEDS Pines de señalización (puerto B)
  * @brief LEDs de estado en GPIOB.
  * @{
  */

/** @brief LED de estado (GPIOB, PIN_0). */
#define GPIO_LED_STATE      GPIO_PIN_0
/** @brief LED de error (GPIOB, PIN_2). */
#define GPIO_LED_ERROR      GPIO_PIN_2
/** @} */

/**
  * @fn void Error_Handler(void)
  * @brief Manejador global de errores fatales.
  * @details Detiene la ejecución en un bucle y puede ser utilizado para
  *          reportar/diagnosticar condiciones críticas. Implementado en @ref main.c.
  */
void Error_Handler(void);

#endif /* __MAIN_H */

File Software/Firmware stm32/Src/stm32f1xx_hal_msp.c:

/**
  ******************************************************************************
  * @file         stm32f1xx_hal_msp.c
  * @brief        This file provides code for the MSP Initialization
  *               and de-Initialization codes.
  ******************************************************************************
  * @attention
  *
  * Copyright (c) 2025 STMicroelectronics.
  * All rights reserved.
  *
  * This software is licensed under terms that can be found in the LICENSE file
  * in the root directory of this software component.
  * If no LICENSE file comes with this software, it is provided AS-IS.
  *
  ******************************************************************************
  */

#include "main.h"

extern DMA_HandleTypeDef hdma_spi2_tx;
extern DMA_HandleTypeDef hdma_spi2_rx;

/**
  * Initializes the Global MSP.
  */
void HAL_MspInit(void) {
  __HAL_RCC_AFIO_CLK_ENABLE();
  __HAL_RCC_PWR_CLK_ENABLE();
  __HAL_AFIO_REMAP_SWJ_NOJTAG();
}

/**
* @brief SPI MSP Initialization
* This function configures the hardware resources used in this example
* @param hspi: SPI handle pointer
* @retval None
*/
void HAL_SPI_MspInit(SPI_HandleTypeDef* hspi) {
  GPIO_InitTypeDef GPIO_InitStruct = {0};
  if(hspi->Instance==SPI2) {
    __HAL_RCC_SPI2_CLK_ENABLE();

    __HAL_RCC_GPIOB_CLK_ENABLE();
    /**SPI2 GPIO Configuration
    PB12     ------> SPI2_NSS
    PB13     ------> SPI2_SCK
    PB14     ------> SPI2_MISO
    PB15     ------> SPI2_MOSI
    */
    GPIO_InitStruct.Pin = GPIO_PIN_12|GPIO_PIN_13|GPIO_PIN_15;
    GPIO_InitStruct.Mode = GPIO_MODE_INPUT;
    GPIO_InitStruct.Pull = GPIO_NOPULL;
    HAL_GPIO_Init(GPIOB, &GPIO_InitStruct);

    GPIO_InitStruct.Pin = GPIO_PIN_14;
    GPIO_InitStruct.Mode = GPIO_MODE_AF_PP;
    GPIO_InitStruct.Speed = GPIO_SPEED_FREQ_HIGH;
    HAL_GPIO_Init(GPIOB, &GPIO_InitStruct);

    hdma_spi2_tx.Instance = DMA1_Channel5;
    hdma_spi2_tx.Init.Direction = DMA_MEMORY_TO_PERIPH;
    hdma_spi2_tx.Init.PeriphInc = DMA_PINC_DISABLE;
    hdma_spi2_tx.Init.MemInc = DMA_MINC_ENABLE;
    hdma_spi2_tx.Init.PeriphDataAlignment = DMA_PDATAALIGN_BYTE;
    hdma_spi2_tx.Init.MemDataAlignment = DMA_MDATAALIGN_BYTE;
    hdma_spi2_tx.Init.Mode = DMA_NORMAL;
    hdma_spi2_tx.Init.Priority = DMA_PRIORITY_LOW;
    if (HAL_DMA_Init(&hdma_spi2_tx) != HAL_OK) {
      Error_Handler();
    }

    __HAL_LINKDMA(hspi,hdmatx,hdma_spi2_tx);

    hdma_spi2_rx.Instance = DMA1_Channel4;
    hdma_spi2_rx.Init.Direction = DMA_PERIPH_TO_MEMORY;
    hdma_spi2_rx.Init.PeriphInc = DMA_PINC_DISABLE;
    hdma_spi2_rx.Init.MemInc = DMA_MINC_ENABLE;
    hdma_spi2_rx.Init.PeriphDataAlignment = DMA_PDATAALIGN_BYTE;
    hdma_spi2_rx.Init.MemDataAlignment = DMA_MDATAALIGN_BYTE;
    hdma_spi2_rx.Init.Mode = DMA_NORMAL;
    hdma_spi2_rx.Init.Priority = DMA_PRIORITY_LOW;
    if (HAL_DMA_Init(&hdma_spi2_rx) != HAL_OK) {
      Error_Handler();
    }

    __HAL_LINKDMA(hspi,hdmarx,hdma_spi2_rx);

    HAL_NVIC_SetPriority(SPI2_IRQn, 0, 0);
    HAL_NVIC_EnableIRQ(SPI2_IRQn);
  }

}

/**
* @brief SPI MSP De-Initialization
* This function freeze the hardware resources used in this example
* @param hspi: SPI handle pointer
* @retval None
*/
void HAL_SPI_MspDeInit(SPI_HandleTypeDef* hspi) {
  if(hspi->Instance==SPI2) {
    __HAL_RCC_SPI2_CLK_DISABLE();

    /**SPI2 GPIO Configuration
    PB12     ------> SPI2_NSS
    PB13     ------> SPI2_SCK
    PB14     ------> SPI2_MISO
    PB15     ------> SPI2_MOSI
    */
    HAL_GPIO_DeInit(GPIOB, GPIO_PIN_12|GPIO_PIN_13|GPIO_PIN_14|GPIO_PIN_15);

    HAL_DMA_DeInit(hspi->hdmatx);
    HAL_DMA_DeInit(hspi->hdmarx);

    HAL_NVIC_DisableIRQ(SPI2_IRQn);
  }
}

/**
* @brief TIM_Base MSP Initialization
* This function configures the hardware resources used in this example
* @param htim_base: TIM_Base handle pointer
* @retval None
*/
void HAL_TIM_Base_MspInit(TIM_HandleTypeDef* htim_base) {
  if(htim_base->Instance==TIM2) {
    __HAL_RCC_TIM2_CLK_ENABLE();
    HAL_NVIC_SetPriority(TIM2_IRQn, 0, 0);
    HAL_NVIC_EnableIRQ(TIM2_IRQn);
  } else if(htim_base->Instance==TIM3) {
    __HAL_RCC_TIM3_CLK_ENABLE();
    HAL_NVIC_SetPriority(TIM3_IRQn, 0, 0);
    HAL_NVIC_EnableIRQ(TIM3_IRQn);
  }
}

/**
* @brief TIM_Base MSP De-Initialization
* This function freeze the hardware resources used in this example
* @param htim_base: TIM_Base handle pointer
* @retval None
*/
void HAL_TIM_Base_MspDeInit(TIM_HandleTypeDef* htim_base) {
  if(htim_base->Instance==TIM2) {
    __HAL_RCC_TIM2_CLK_DISABLE();
    HAL_NVIC_DisableIRQ(TIM2_IRQn);
  } else if(htim_base->Instance==TIM3) {
    __HAL_RCC_TIM3_CLK_DISABLE();
    HAL_NVIC_DisableIRQ(TIM3_IRQn);
  }
}

/**
* @brief UART MSP Initialization
* This function configures the hardware resources used in this example
* @param huart: UART handle pointer
* @retval None
*/
void HAL_UART_MspInit(UART_HandleTypeDef* huart) {
  GPIO_InitTypeDef GPIO_InitStruct = {0};
  if(huart->Instance==USART1) {
    __HAL_RCC_USART1_CLK_ENABLE();
    __HAL_RCC_GPIOB_CLK_ENABLE();

    GPIO_InitStruct.Pin = GPIO_PIN_6;
    GPIO_InitStruct.Mode = GPIO_MODE_AF_PP;
    GPIO_InitStruct.Speed = GPIO_SPEED_FREQ_HIGH;
    HAL_GPIO_Init(GPIOB, &GPIO_InitStruct);

    GPIO_InitStruct.Pin = GPIO_PIN_7;
    GPIO_InitStruct.Mode = GPIO_MODE_INPUT;
    GPIO_InitStruct.Pull = GPIO_NOPULL;
    HAL_GPIO_Init(GPIOB, &GPIO_InitStruct);

    __HAL_AFIO_REMAP_USART1_ENABLE();
  }

}

/**
* @brief UART MSP De-Initialization
* This function freeze the hardware resources used in this example
* @param huart: UART handle pointer
* @retval None
*/
void HAL_UART_MspDeInit(UART_HandleTypeDef* huart) {
  if(huart->Instance==USART1) {
    __HAL_RCC_USART1_CLK_DISABLE();

    HAL_GPIO_DeInit(GPIOB, GPIO_PIN_6|GPIO_PIN_7);
  }

}
